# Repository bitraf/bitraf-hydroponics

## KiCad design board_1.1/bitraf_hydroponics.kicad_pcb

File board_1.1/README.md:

TODO:
* Rearrange MOSFETs so they work as expected

QUESTIONS:
* Do we need the exra pins going to GND on rotary encoder and programing headers if we go for the jumper solution?

FEATURES:
* Fuse for power ports?

DONE:
* Added "0ohm" pull-up between VCC -> CH_PD
* Added 10k pull-up between GPIO2 -> 3.3v
* Added jumper connector to pull-down RESET and GPIO0 -> GND

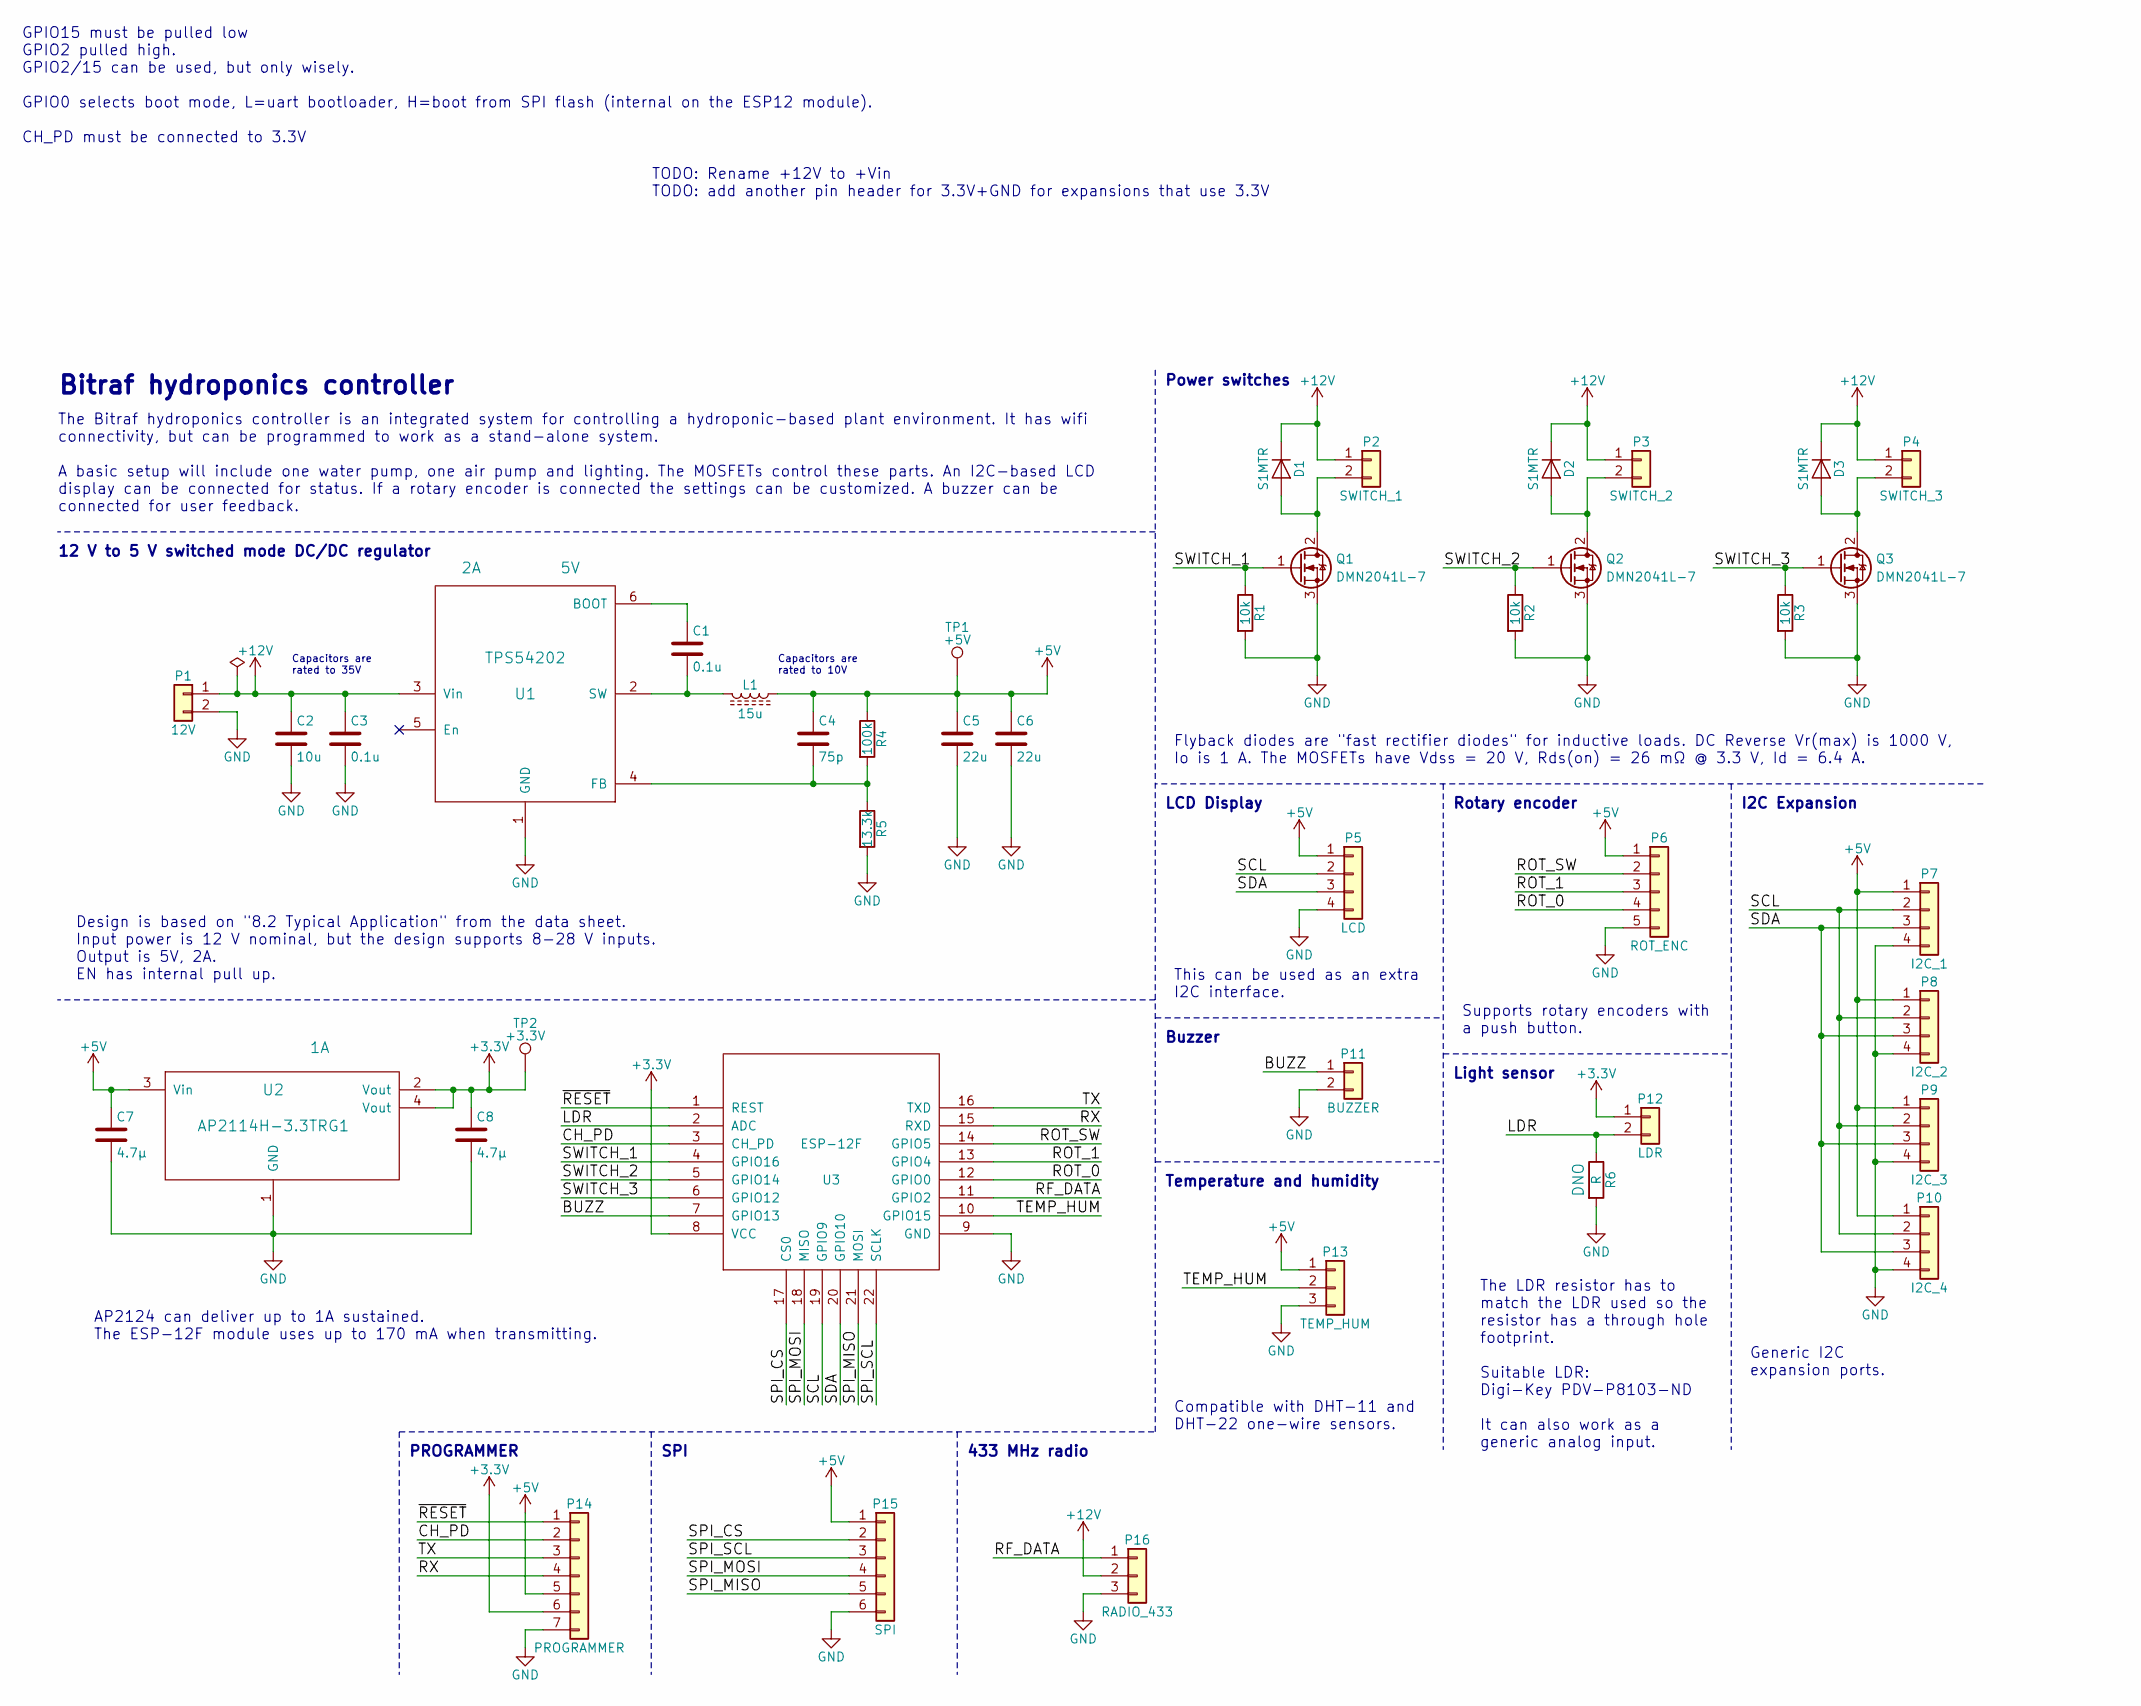
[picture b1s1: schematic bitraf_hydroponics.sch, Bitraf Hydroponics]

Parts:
C1: 0.1u; C_0805; voltage 10V; mpn CL21B104MBCNNNC
C2: 10u; C_0805; mpn GMK212BBJ106KG-T
C3: 0.1u; C_0805; mpn GMK212BJ104KGHT
C4: 75p; C_0805; voltage 10V; mpn 08051A750JAT2A
C5, C6: 22u; C_0805; voltage 10V; mpn CL21A226MQCLQNC
C7, C8: 4.7µ; C_0805; mpn LMK212BJ475KD-T
D1, D2, D3: S1MTR; D_SMA_Handsoldering; mpn S1MTR; digikey 1655-1506-2-ND
L1: 15u; L_Taiyo-Yuden_NR-80xx; mpn NRS8040T150MJGJ
P1: 12V; PhoenixContact_PTSM0,5_2-2,5-H_SMD; mpn 1702473
P2: SWITCH_1; PhoenixContact_PTSM0,5_2-2,5-H_SMD; mpn 1702473
P3: SWITCH_2; PhoenixContact_PTSM0,5_2-2,5-H_SMD; mpn 1702473
P4: SWITCH_3; PhoenixContact_PTSM0,5_2-2,5-H_SMD; mpn 1702473
P5: LCD; Pin_Header_Straight_1x04_Pitch2.54mm; mpn 826926-5
P6: ROT_ENC; Pin_Header_Straight_1x05_Pitch2.54mm; mpn 826926-5
P7: I2C_1; Pin_Header_Straight_1x04_Pitch2.54mm; mpn 826926-4
P8: I2C_2; Pin_Header_Straight_1x04_Pitch2.54mm; mpn 826926-4
P9: I2C_3; Pin_Header_Straight_1x04_Pitch2.54mm; mpn 826926-4
P10: I2C_4; Pin_Header_Straight_1x04_Pitch2.54mm; mpn 826926-4
P11: BUZZER; PhoenixContact_PTSM0,5_2-2,5-H_SMD; mpn 1702473
P12: LDR; PhoenixContact_PTSM0,5_2-2,5-H_SMD; mpn 1702473
P13: TEMP_HUM; Pin_Header_Straight_1x03_Pitch2.54mm; mpn 826926-3
P14: PROGRAMMER; Pin_Header_Straight_1x07_Pitch2.54mm
P15: SPI; Pin_Header_Straight_1x06_Pitch2.54mm; mpn 826926-6
P16: RADIO_433; Socket_Strip_Straight_1x03_Pitch2.54mm; mpn PPPC031LFBN-RC
Q1, Q2, Q3: DMN2041L-7; SOT-23; mpn DMN2041L-7
R1, R2, R3: 10k; R_0805; mpn RC0805FR-0710KL
R4: 100k; R_0805; mpn RC0805FR-07100KL
R5: 13.3k; R_0805; mpn RC0805FR-0713K3L
R6: R; R_Axial_DIN0207_L6.3mm_D2.5mm_P10.16mm_Horizontal
TP1: +5V; Test_Point_Pad_d1.0mm
TP2: +3.3V; Test_Point_Pad_d1.0mm
U1: TPS54202; SOT-23-6_Handsoldering; mpn TPS54202DDCT
U2: AP2114H-3.3TRG1; SOT-223; mpn AP2114H-3.3TRG1
U3: ESP-12F; ESP-12E

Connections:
+3V3: C8.1, P12.1, P14.6, TP2.1, U2.2 (Vout), U2.4 (Vout), U3.8 (VCC)
+5V: C4.1, C5.1, C6.1, C7.1, L1.1, P5.1, P6.1, P7.1, P8.1, P9.1, P10.1, P13.1, P14.5, P15.1, R4.1, TP1.1, U2.3 (Vin)
+12V: C2.1, C3.1, D1.1 (K), D2.1 (K), D3.1 (K), P1.1, P2.1, P3.1, P4.1, P16.2, U1.3 (Vin)
/BUZZ: P11.1, U3.7 (GPIO13)
/CH_PD: P14.2, U3.3 (CH_PD)
/LDR: P12.2, R6.1, U3.2 (ADC)
/RF_DATA: P16.1, U3.11 (GPIO2)
/ROT_0: P6.4, U3.12 (GPIO0)
/ROT_1: P6.3, U3.13 (GPIO4)
/ROT_SW: P6.2, U3.14 (GPIO5)
/RX: P14.4, U3.15 (RXD)
/SCL: P5.2, P7.2, P8.2, P9.2, P10.2, U3.19 (GPIO9)
/SDA: P5.3, P7.3, P8.3, P9.3, P10.3, U3.20 (GPIO10)
/SPI_CS: P15.2, U3.17 (CS0)
/SPI_MISO: P15.5, U3.21 (MOSI)
/SPI_MOSI: P15.4, U3.18 (MISO)
/SPI_SCL: P15.3, U3.22 (SCLK)
/SWITCH_1: Q1.1 (G), R1.1, U3.4 (GPIO16)
/SWITCH_2: Q2.1 (G), R2.1, U3.5 (GPIO14)
/SWITCH_3: Q3.1 (G), R3.1, U3.6 (GPIO12)
/TEMP_HUM: P13.2, U3.10 (GPIO15)
/TX: P14.3, U3.16 (TXD)
/~RESET: P14.1, U3.1 (REST)
GND: C2.2, C3.2, C5.2, C6.2, C7.2, C8.2, P1.2, P5.4, P6.5, P7.4, P8.4, P9.4, P10.4, P11.2, P13.3, P14.7, P15.6, P16.3, Q1.3 (S), Q2.3 (S), Q3.3 (S), R1.2, R2.2, R3.2, R5.2, R6.2, U1.1 (GND), U2.1 (GND), U3.9 (GND)
unnamed: C1.1, U1.6 (BOOT)
unnamed: C1.2, L1.2, U1.2 (SW)
unnamed: C4.2, R4.2, R5.1, U1.4 (FB)
unnamed: D1.2 (A), P2.2, Q1.2 (D)
unnamed: D2.2 (A), P3.2, Q2.2 (D)
unnamed: D3.2 (A), P4.2, Q3.2 (D)

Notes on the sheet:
Generic I2C expansion ports.
The LDR resistor has to match the LDR used so the resistor has a through hole footprint. Suitable LDR: Digi-Key PDV-P8103-ND It can also work as a generic analog input.
Rotary encoder
I2C Expansion
Temperature and humidity
Compatible with DHT-11 and DHT-22 one-wire sensors.
Supports rotary encoders with a push button.
Buzzer
Light sensor
LCD Display
433 MHz radio
Flyback diodes are "fast rectifier diodes" for inductive loads. DC Reverse Vr(max) is 1000 V, Io is 1 A. The MOSFETs have Vdss = 20 V, Rds(on) = 26 mΩ @ 3.3 V, Id = 6.4 A.
Power switches
Design is based on "8.2 Typical Application" from the data sheet. Input power is 12 V nominal, but the design supports 8-28 V inputs. Output is 5V, 2A. EN has internal pull up.
SPI
PROGRAMMER
AP2124 can deliver up to 1A sustained. The ESP-12F module uses up to 170 mA when transmitting.
Bitraf hydroponics controller
The Bitraf hydroponics controller is an integrated system for controlling a hydroponic-based plant environment. It has wifi connectivity, but can be programmed to work as a stand-alone system. A basic setup will include one water pump, one air pump and lighting. The MOSFETs control these parts. An 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
This can be used as an extra I2C interface.
12 V to 5 V switched mode DC/DC regulator
Capacitors are rated to 35V
Capacitors are rated to 10V
TODO: Rename +12V to +Vin TODO: add another pin header for 3.3V+GND for expansions that use 3.3V
GPIO15 must be pulled low GPIO2 pulled high. GPIO2/15 can be used, but only wisely. GPIO0 selects boot mode, L=uart bootloader, H=boot from SPI flash (internal on the ESP12 module). CH_PD must be connected to 3.3V

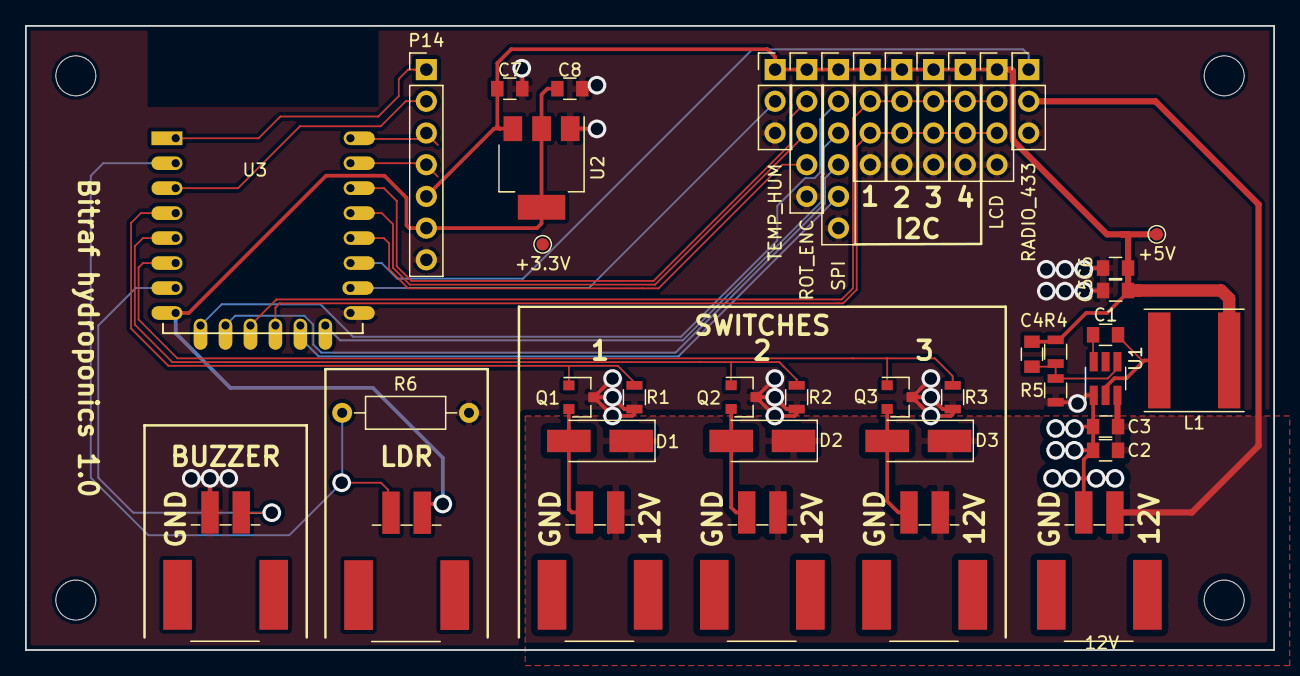
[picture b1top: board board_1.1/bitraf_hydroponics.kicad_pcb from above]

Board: 2 copper layers, 100.0 x 50.0 mm, 42 parts (0 on the bottom side), 30 nets.

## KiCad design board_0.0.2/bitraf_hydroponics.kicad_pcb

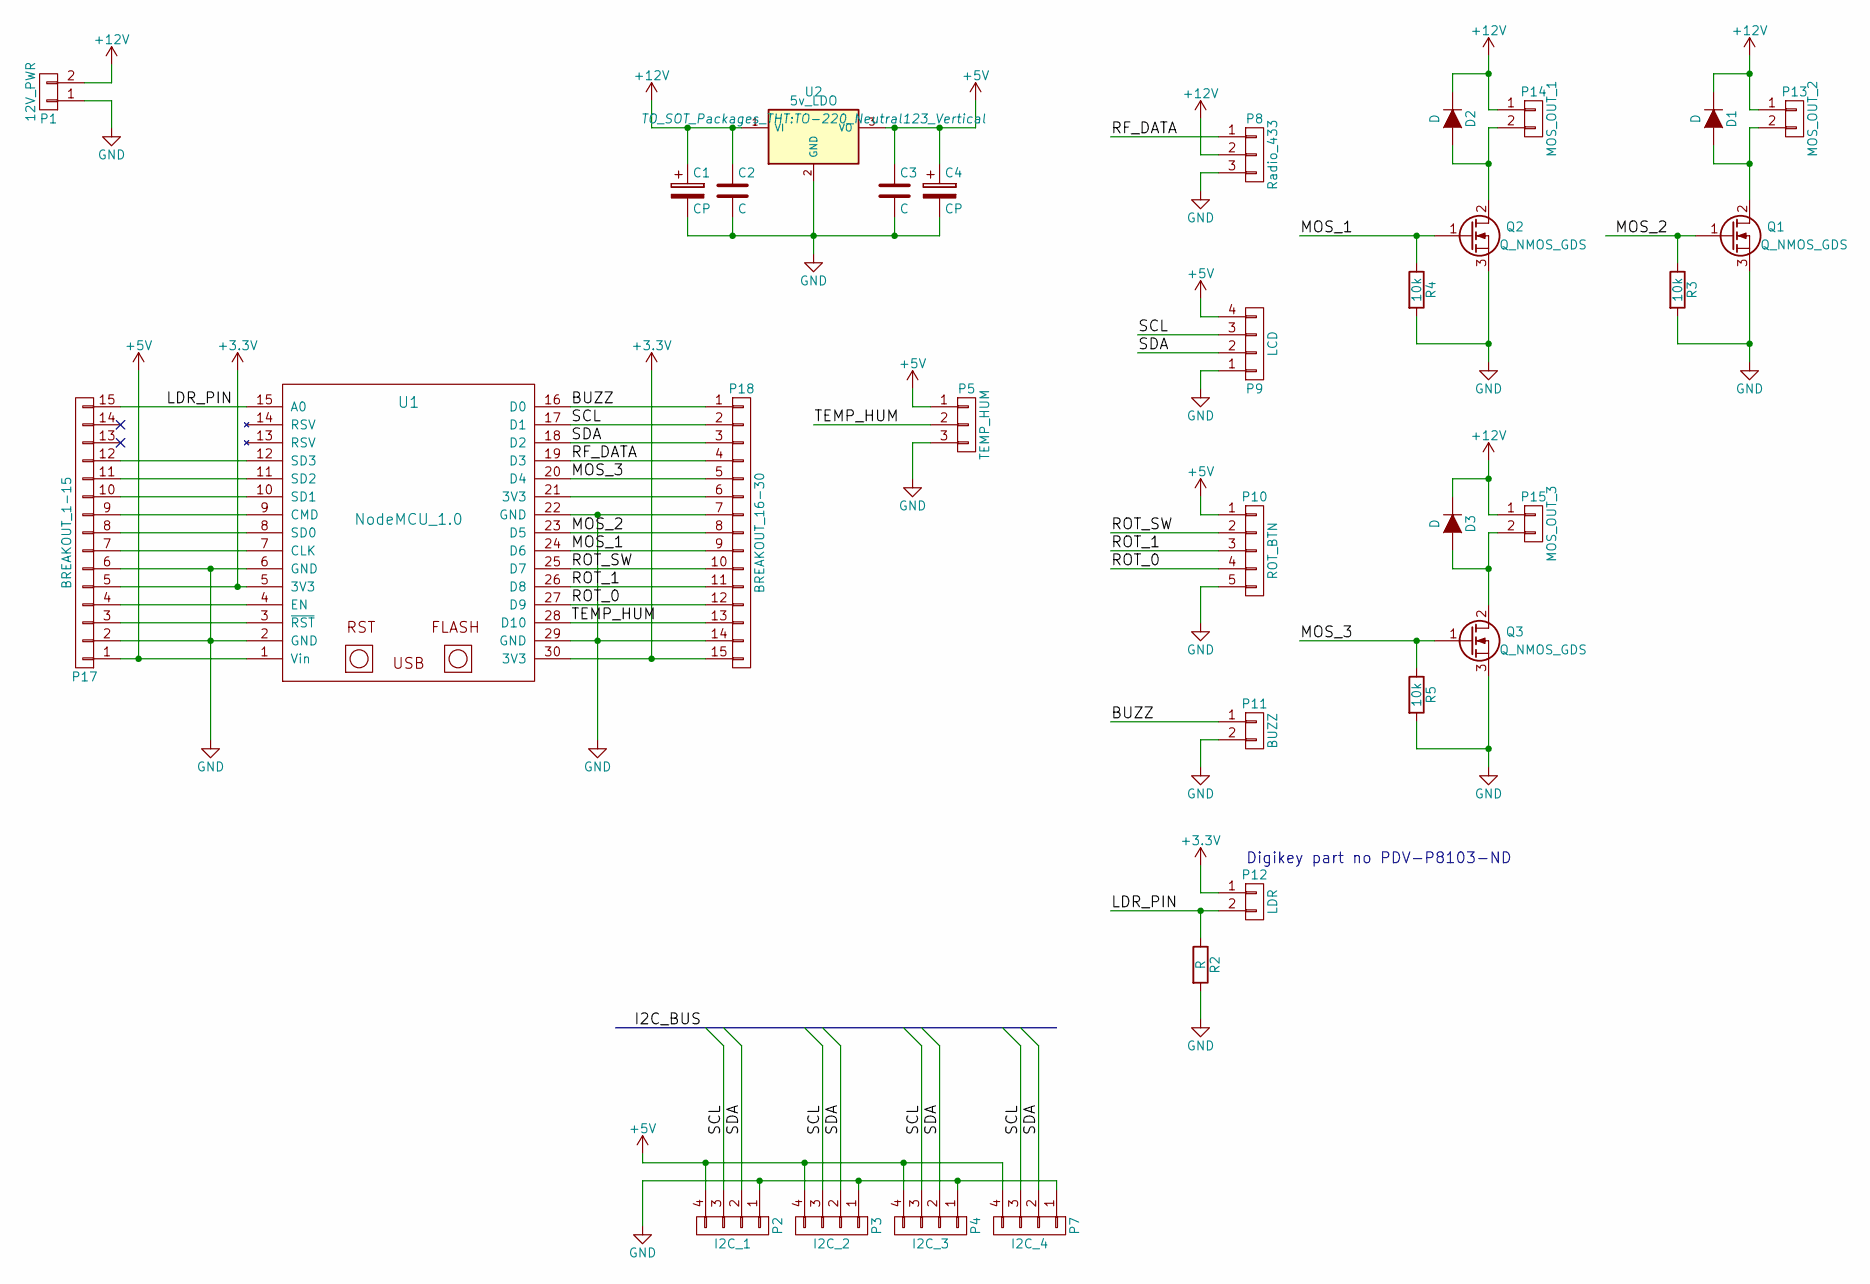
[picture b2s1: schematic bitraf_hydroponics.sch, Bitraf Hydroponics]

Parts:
C1, C4: CP; C_Radial_D5_L6_P2.5
C2, C3: C; C_Disc_D3_P2.5
D1, D2, D3: D; Diode_DO-41_SOD81_Horizontal_RM10
P1: 12V_PWR; TerminalBlock_Pheonix_MKDS1.5-2pol
P2: I2C_1; Pin_Header_Straight_1x04
P3: I2C_2; Pin_Header_Straight_1x04
P4: I2C_3; Pin_Header_Straight_1x04
P5: TEMP_HUM; Pin_Header_Straight_1x03
P7: I2C_4; Pin_Header_Straight_1x04
P8: Radio_433; Pin_Header_Straight_1x03
P9: LCD; Pin_Header_Straight_1x04
P10: ROT_BTN; Pin_Header_Straight_1x05
P11: BUZZ; Pin_Header_Straight_1x02
P12: LDR; Pin_Header_Straight_1x02
P13: MOS_OUT_2; TerminalBlock_Pheonix_MKDS1.5-2pol
P14: MOS_OUT_1; TerminalBlock_Pheonix_MKDS1.5-2pol
P15: MOS_OUT_3; TerminalBlock_Pheonix_MKDS1.5-2pol
P17: BREAKOUT_1-15; Pin_Header_Straight_1x15
P18: BREAKOUT_16-30; Pin_Header_Straight_1x15
Q1, Q2, Q3: Q_NMOS_GDS; TO-220_Neutral123_Vertical
R2: R; Resistor_Horizontal_RM10mm
R3, R4, R5: 10k; Resistor_Horizontal_RM10mm
U1: NodeMCU_1.0; NodeMCU
U2: 5v_LDO; TO-220_Neutral123_Vertical

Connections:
+3V3: P12.1, P17.5, P18.15, U1.5 (3V3), U1.30 (3V3)
+5V: C3.1, C4.1, P2.4, P3.4, P4.4, P5.1, P7.4, P9.4, P10.1, P17.1, U1.1 (Vin), U2.3 (VO)
+12V: C1.1, C2.1, D1.1 (K), D2.1 (K), D3.1 (K), P1.2, P8.2, P13.1, P14.1, P15.1, U2.1 (VI)
/BUZZ: P11.1, P18.1, U1.16 (D0)
/LDR_PIN: P12.2, P17.15, R2.1, U1.15 (A0)
/MOS_1: P18.9, Q2.1 (G), R4.1, U1.24 (D6)
/MOS_2: P18.8, Q1.1 (G), R3.1, U1.23 (D5)
/MOS_3: P18.5, Q3.1 (G), R5.1, U1.20 (D4)
/RF_DATA: P8.1, P18.4, U1.19 (D3)
/ROT_0: P10.4, P18.12, U1.27 (D9)
/ROT_1: P10.3, P18.11, U1.26 (D8)
/ROT_SW: P10.2, P18.10, U1.25 (D7)
/SCL: P2.3, P3.3, P4.3, P7.3, P9.3, P18.2, U1.17 (D1)
/SDA: P2.2, P3.2, P4.2, P7.2, P9.2, P18.3, U1.18 (D2)
/TEMP_HUM: P5.2, P18.13, U1.28 (D10)
GND: C1.2, C2.2, C3.2, C4.2, P1.1, P2.1, P3.1, P4.1, P5.3, P7.1, P8.3, P9.1, P10.5, P11.2, P17.2, P17.6, P18.7, P18.14, Q1.3 (S), Q2.3 (S), Q3.3 (S), R2.2, R3.2, R4.2, R5.2, U1.2 (GND), U1.6 (GND), U1.22 (GND), U1.29 (GND), U2.2 (GND)
unnamed: D1.2 (A), P13.2, Q1.2 (D)
unnamed: D2.2 (A), P14.2, Q2.2 (D)
unnamed: D3.2 (A), P15.2, Q3.2 (D)
unnamed: P17.3, U1.3 (~RST)
unnamed: P17.4, U1.4 (EN)
unnamed: P17.7, U1.7 (CLK)
unnamed: P17.8, U1.8 (SD0)
unnamed: P17.9, U1.9 (CMD)
unnamed: P17.10, U1.10 (SD1)
unnamed: P17.11, U1.11 (SD2)
unnamed: P17.12, U1.12 (SD3)
unnamed: P18.6, U1.21 (3V3)

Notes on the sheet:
Digikey part no PDV-P8103-ND

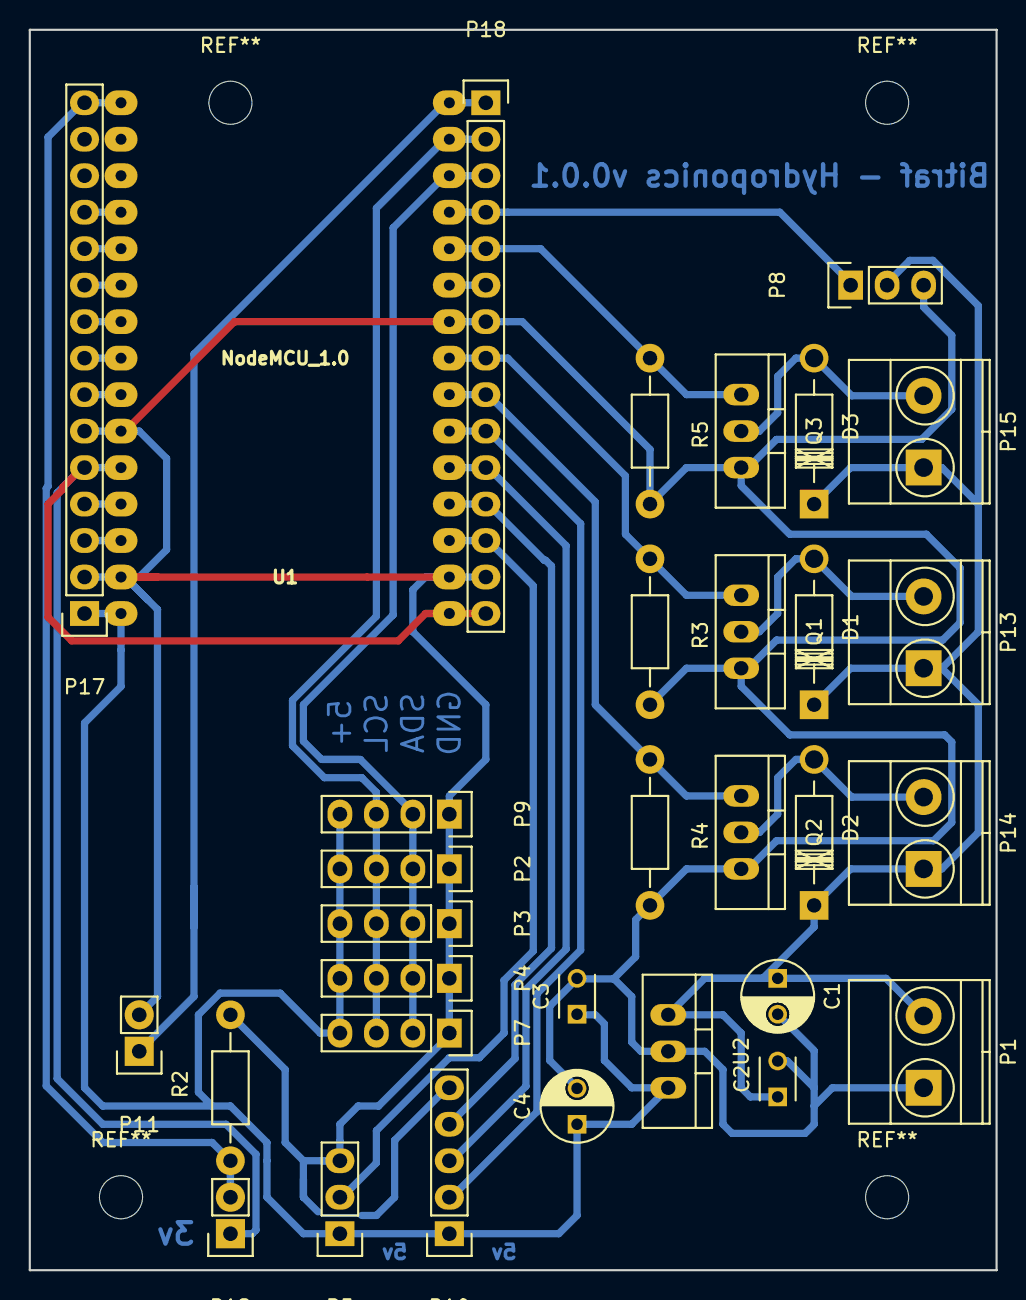
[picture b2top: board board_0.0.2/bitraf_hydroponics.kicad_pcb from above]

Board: 2 copper layers, 67.3 x 86.4 mm, 32 parts (0 on the bottom side), 28 nets.

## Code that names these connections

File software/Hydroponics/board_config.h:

#define DEVICE_ID "hydroponics-1"

#define MQTT_ADDRESS "mqtt.bitraf.no"
#define MQTT_PORT 1883
#define MQTT_CLIENT_ID DEVICE_ID

#define FORMAT_SPIFFS false


// NodeMCU
#if defined ARDUINO_ESP8266_NODEMCU
  // RF transmit
  #define RF_DATA D4

  // Switches
  #define SWITCH_1 D0
  #define SWITCH_2 D5
  #define SWITCH_3 D6

  // Rotary encoder
  #define ROT_0 D3
  #define ROT_1 D2
  #define ROT_SW D1

  // Buzzer
  #define BUZZ D7

  // Temp hum
  #define TEMP_HUM D8

  // LDR
  #define LDR A0

// ESP8266 Chip only
#elif defined ARDUINO_ESP8266_ESP01
  // RF transmit
  #define RF_DATA 11

  // Switches
  #define SWITCH_1 4
  #define SWITCH_2 5
  #define SWITCH_3 6

  // Rotary encoder
  #define ROT_0 12
  #define ROT_1 13
  #define ROT_SW 14

  // Buzzer
  #define BUZZ 7

  // Temp hum
  #define TEMP_HUM 10

  // LDR
  #define LDR 2

#endif

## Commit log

2016-09-22 first aproach on schema ready. Begun placing parts
2016-09-28 o A FreeCAD model of IKEA Kuggis.
2016-09-29 Getting on with placing and tracing
2016-09-30 Parts placed and traced. Need to define board and ground plane
2016-10-02 added mounting holes, edge cut and copper fill
2016-10-04 new stand pipe with double dribble action!
2016-10-04 tweaked o-ring size
2016-10-04 for slicing
2016-10-04 got nuts?
2016-10-06 Added the first file
2016-10-06 o Adding display and button mount. Should be moved out to a separate file.
2016-10-06 Added the i2c display library
2016-10-06 o Rotary encoder, go!
2016-10-13 adjusted screw end. Expanded siphon and double siphon tubes
2016-10-13 adjusted mini siphon to avoid gaps aka leaks
2016-10-14 A bit hasty in my commit.
2016-10-16 wider o-ring cavity and quadripple siphon action
2016-11-10 o Moving all tracks to back side. o Fixing some DRC issues.
2017-01-12 new revision
2017-01-12 not quite sure what changed..
2017-01-12 o Adding support for OTA.
2017-01-12 fixed Vin bug. Traced new route for buzz and ldr. Added resistors to terminals
2017-03-08 NTP and MQTT initial implementaton. We may now set lights on/off through MQTT
2017-03-08 Need these to control lights
2017-03-09 nitial commit
2017-03-09 Updated Kuggis, moar accurate model
2017-03-09 Updated Kuggis, removed panel
2017-04-20 sort of functioning code.
2017-04-27 works, but still quite messy. About to refactor storing/fetching of persistent data
2017-04-27 changed name of device
2017-04-27 now with air pump alarm. Spaghetti wet wet wet code, but seems to work.
2017-05-04 WORKS!
2017-05-07 removed counter in phoneHome to avoid possible mangled int. Also reverted to print the whole settings.json on status topic appending refactor of the whole status idea
2017-05-11 Added status topic with dynamic info. moved mqtt topics into this file. Also loop through them to make sure all of them get registered.
2017-05-18 Added option to override light
2017-05-18 removed wifi from json settings. may have caused issues and won't be useful yet
2017-06-01 Dynamic hostname based on DEVICE_ID
2017-06-01 Toggle lights and air on of by passing 'now' to the topic
2017-06-01 added an example wifipassword.h as a comment
2017-06-01 filltime status returns in seconds
2017-06-01 added publishing from lights on/off and air on/off
2017-06-19 moved i2c bus out of the way for USB and rerouted. Also removed resistors over terminals
2017-06-26 refactored readsettings and begun an other aproach at overriding light and air
2017-06-26 think override of ligths and air works like they should now.
2017-06-27 merged air on/off and ligths on/off to toggleAir/Lights function. Also merged checkLights/Air to a checkAction function
2017-06-28 updated checkAction function to handle all variations of time settings
2017-06-28 removed comment
2017-06-28 Think I actually got the alarm logic to work with most combinations of times
2017-06-29 switched to static json buffer
2017-07-04 got head out of my ass and refactored checkAction function
2017-09-15 cleanup
2017-09-15 adjustet height of funnel
2017-10-05 pcb: not exactly sure what I did, but it passes the tests. Models: tweaked to work with the low kuggis bed. New dome fits perfectly over stand pipe
2017-10-07 o Refreshing footprints with updated KiCAD libraries. All parts have 3D-models now except the NodeMCU. o Adding some more text on the copper. o Fixing a couple of ERC warnings.
2017-10-12 Initial import of rev 1.0. Main features: o Almost all SMD components. o Using a switching regulator instead of LDO for 12 -> 5V convertion. o Adding SPI output.
2017-10-19 o Removing old PCB layout.
2017-10-19 o Replacing NodeMCU with a single ESP-12F module and an LDO. Will need an external programmer.
2017-10-20 o Adding missing ESP8266 repository.
2017-10-20 o Selecting components for flyback diodes. o Adding footprints for MOSFETs. o More comments.
2017-10-25 o Selecting the rest of the footprints. Using 0805 as default SMD size to make it makerspace friendly. o Some more nitpicking.
2017-10-25 rough sort of components
2017-10-26 schematic: o Changing 12V connector to the same as the rest. o Better label for Radio. o Changing R6 from SMD to THT so it is easier to customize with the LDR. pcb: o Adding copper zones connected to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
2017-10-26 switched position on SDA and SCL on the LCD header to match the rest of I2C bus
2017-10-26 everything connected. Ugly and thin tracks where they should be wider, but passes test.
2017-10-26 Hmm. found a few unconnected Gnd's not picked up by test
2017-10-27 o Updating the symbol of P1 so it matches the other symbols.
2017-10-27 o Removing unused nodemcu symbols.
2017-10-27 o Better path for the ESP lib.
2017-10-27 o Switching from PhoenixContact_PTSM0,5_4-HV-2,5_SMD to PhoenixContact_PTSM0,5_2-2,5-H_SMD.
2017-10-27 o Renaming BUZZ to BUZZER now that it is visible on the PCB.
2017-10-27 o Switching to new footprints for connectors. Moves everything around a little bit. o Adding some silk screen text to better indicate what goes where.
2017-10-27 o Adding dimmensions on fab layer.
2017-10-28 o Adding datasheet for MOSFETs.
2017-10-29 o Adding IPython notebook for temperature calculations of the MOSFET.
2017-10-30 o My build tools.
2017-11-08 o Sorting headers, adding more comments.
2017-11-08 o Adding mpn and other misc stuff. The forgotten commit.
2017-11-08 adjusted pins to match new board design
2017-11-08 refactored loop over topic array to avoid using a variable to determine length of it. Topic array is now NULL termiated
2017-11-08 moved a few global definitions here
2017-11-08 removed definitions of pins and included them from board_config.h
2017-11-09 o Adding GPIO tool.
2017-11-09 added support for both NodeMCU and ESP-12E
2017-11-09 Added pullups and jumper header fro programming. Still need to tweak the mosfets, but need expert help
2017-11-09 This should go in it's own branch/folder. Revert "Added pullups and jumper header fro programming. Still need to tweak the mosfets, but need expert help"
    This reverts commit b0ba335143d29f2dde67b78845eb19ede0b5a3d2.
2017-11-09 o Initial work on a 1.1 revision.
2017-11-09 added pull-ups and jumper connector for programming
2017-11-09 Added a feature suggestion
2017-11-09 fixed faulty pull to GND in the jumper. Added a questions section in the README.md
